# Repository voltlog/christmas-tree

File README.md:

# Voltlog Smart Christmas Tree

This was my attempt at creating a smart Christmass tree decoration. I wanted to have a bunch of RGB LEDs that I could control remotely from my smart home automation system so I created this board using 11 x SK6812-EC20 RGB LEDs connected with an ESP32. The board can be flashed with an arduino sketch and have it flash various patterns in a standalone operating mode or you can flash it with esphome (or other similar platforms) and have it controlled from your smart home system.

More info about this project in [Voltlog #344](https://youtu.be/laZLzfCeY8s).
This was available in a limitted edition in the [Voltlog Tindie Store](https://www.tindie.com/products/voltlog/voltlog-smart-christmas-tree/).

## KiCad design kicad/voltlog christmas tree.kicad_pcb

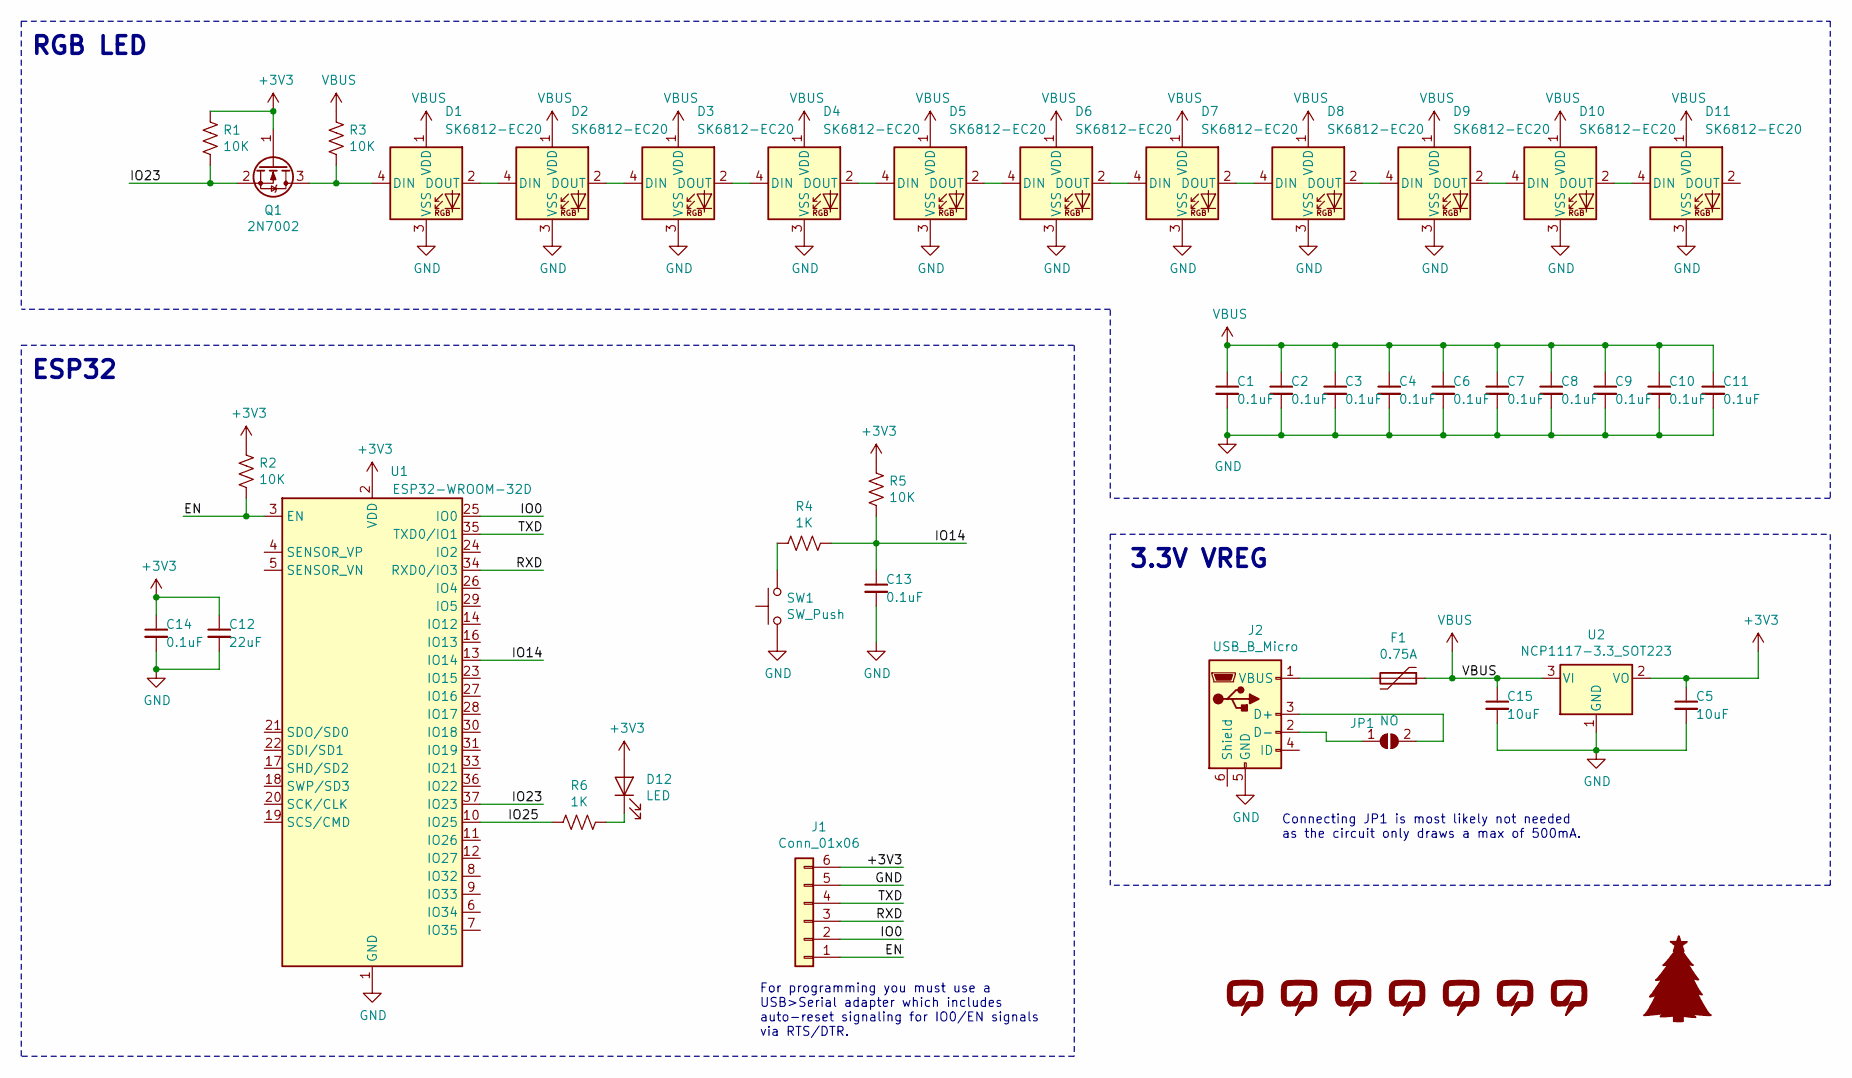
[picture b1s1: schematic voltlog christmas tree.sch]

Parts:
C1, C2, C3, C4, C6, C7, C8, C9, C10, C11, C13, C14: 0.1uF; C_0805_2012Metric
C5, C15: 10uF; C_0805_2012Metric
C12: 22uF; C_0805_2012Metric
D1, D2, D3, D4, D5, D6, D7, D8, D9, D10, D11: SK6812-EC20; sk6812-2020
D12: LED; LED_0805_2012Metric
F1: 0.75A; Fuse_0805_2012Metric
J1: Conn_01x06; JST_SH_BM06B-SRSS-TB_1x06-1MP_P1.00mm_Vertical
J2: USB_B_Micro; USB_Micro-B_Molex-105017-0001
JP1: NO; SolderJumper-2_P1.3mm_Open_RoundedPad1.0x1.5mm
Q1: 2N7002; SOT-23
R1, R2, R3, R5: 10K; R_0805_2012Metric
R4, R6: 1K; R_0805_2012Metric
SW1: SW_Push; SW_Push_1P1T_NO_6x6mm_H9.5mm
T1: ChristmasTree; test
U1: ESP32-WROOM-32D; ESP32-WROOM-32
U2: NCP1117-3.3_SOT223; SOT-223-3_TabPin2
V1, V2, V3, V4, V5, V6, V8: VOLTLOG_LOGO; voltlog_mask_5mm

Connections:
+3V3: C5.1, C12.1, C14.1, D12.2 (A), J1.6, Q1.1 (G), R1.1, R2.1, R5.1, U1.2 (VDD), U2.2 (VO)
/EN: J1.1, R2.2, U1.3 (EN)
/IO0: J1.2, U1.25 (IO0)
/IO14: C13.1, R4.1, R5.2, U1.13 (IO14)
/IO23: Q1.2 (S), R1.2, U1.37 (IO23)
/IO25: R6.2, U1.10 (IO25)
/RXD: J1.3, U1.34 (RXD0/IO3)
/TXD: J1.4, U1.35 (TXD0/IO1)
GND: C1.2, C2.2, C3.2, C4.2, C5.2, C6.2, C7.2, C8.2, C9.2, C10.2, C11.2, C12.2, C13.2, C14.2, C15.2, D1.3 (VSS), D2.3 (VSS), D3.3 (VSS), D4.3 (VSS), D5.3 (VSS), D6.3 (VSS), D7.3 (VSS), D8.3 (VSS), D9.3 (VSS), D10.3 (VSS), D11.3 (VSS), J1.5, J2.5 (GND), SW1.1, U1.1 (GND), U1.15 (GND), U1.38 (GND), U1.39 (GND), U2.1 (GND)
unnamed: D1.2 (DOUT), D2.4 (DIN)
unnamed: D1.4 (DIN), Q1.3 (D), R3.2
unnamed: D2.2 (DOUT), D3.4 (DIN)
unnamed: D3.2 (DOUT), D4.4 (DIN)
unnamed: D4.2 (DOUT), D5.4 (DIN)
unnamed: D5.2 (DOUT), D6.4 (DIN)
unnamed: D6.2 (DOUT), D7.4 (DIN)
unnamed: D7.2 (DOUT), D8.4 (DIN)
unnamed: D8.2 (DOUT), D9.4 (DIN)
unnamed: D10.2 (DOUT), D11.4 (DIN)
unnamed: D9.2 (DOUT), D10.4 (DIN)
unnamed: D12.1 (K), R6.1
unnamed: F1.2, J2.1 (VBUS)
unnamed: J2.2 (D-), JP1.1 (A)
unnamed: J2.3 (D+), JP1.2 (B)
unnamed: R4.2, SW1.2
VBUS: C1.1, C2.1, C3.1, C4.1, C6.1, C7.1, C8.1, C9.1, C10.1, C11.1, C15.1, D1.1 (VDD), D2.1 (VDD), D3.1 (VDD), D4.1 (VDD), D5.1 (VDD), D6.1 (VDD), D7.1 (VDD), D8.1 (VDD), D9.1 (VDD), D10.1 (VDD), D11.1 (VDD), F1.1, R3.1, U2.3 (VI)

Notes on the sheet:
ESP32
3.3V VREG
RGB LED
For programming you must use a USB>Serial adapter which includes auto-reset signaling for IO0/EN signals via RTS/DTR.
Connecting JP1 is most likely not needed as the circuit only draws a max of 500mA.

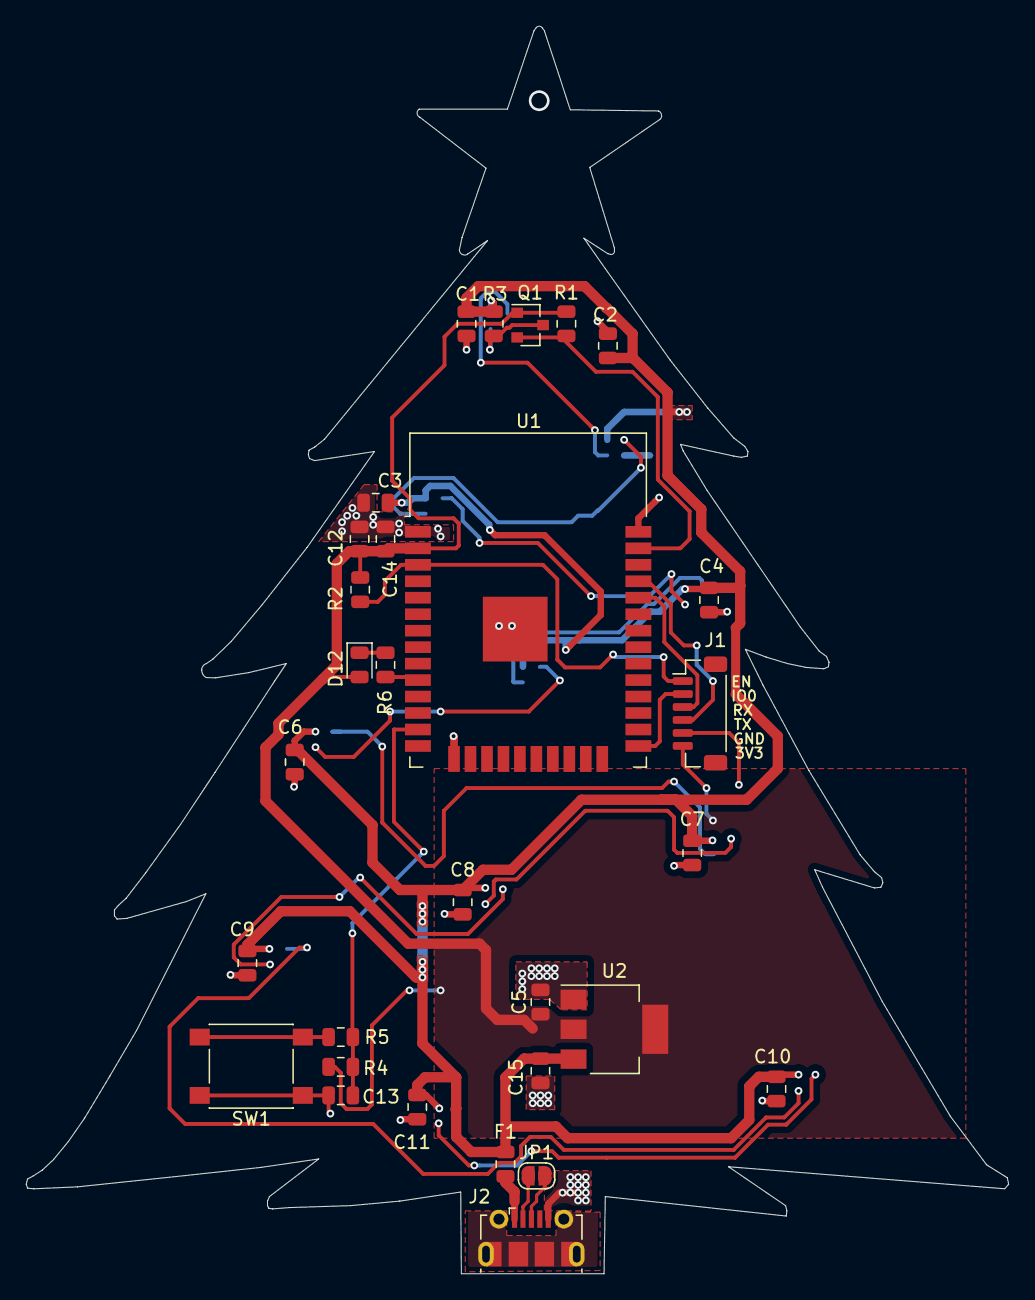
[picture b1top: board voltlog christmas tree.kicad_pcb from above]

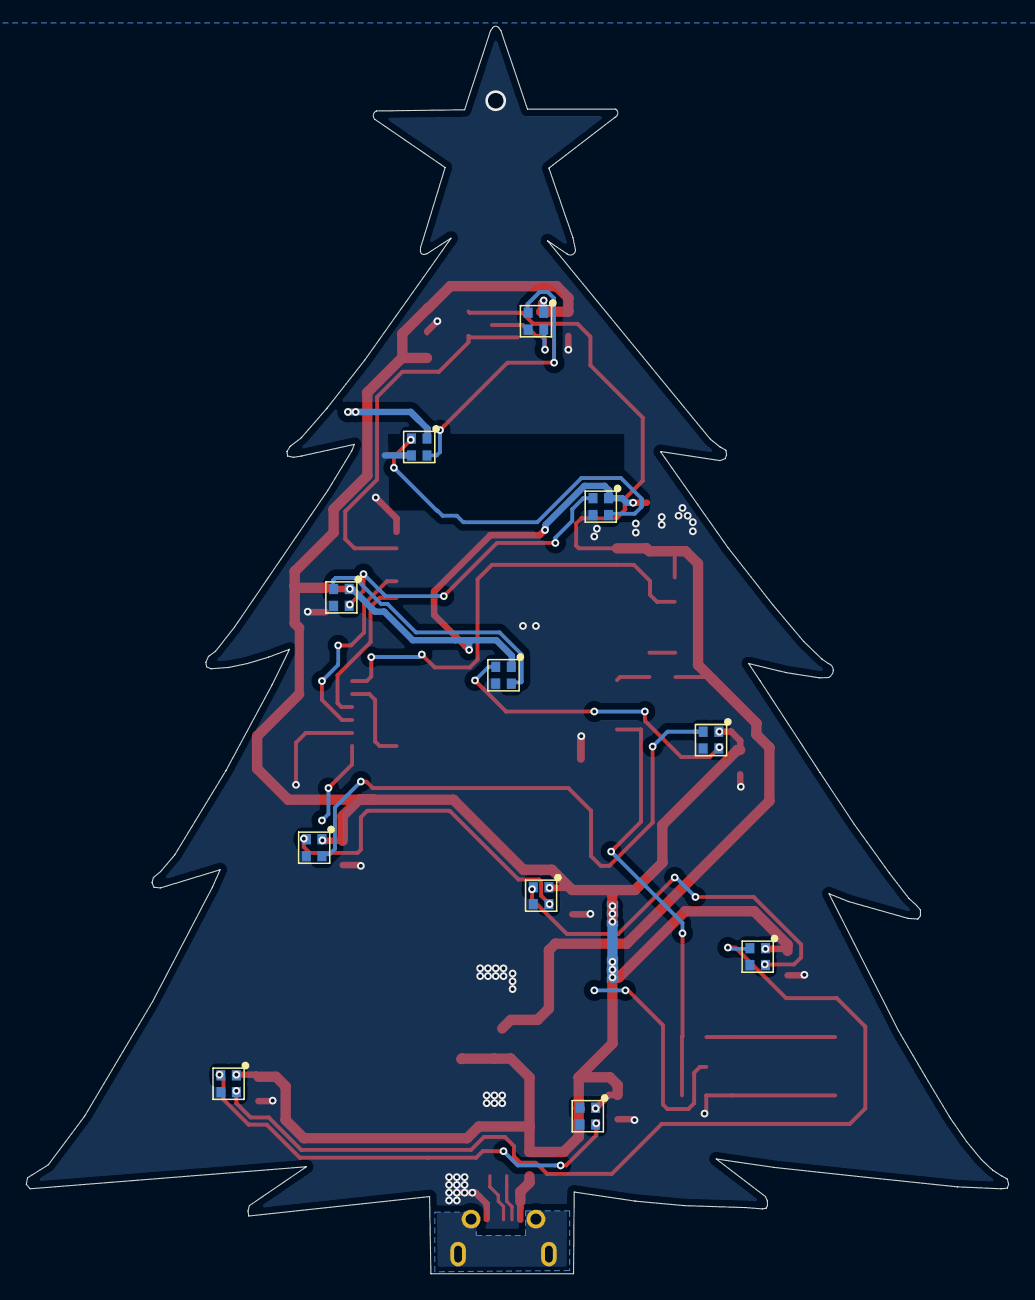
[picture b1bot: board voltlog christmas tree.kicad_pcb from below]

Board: 2 copper layers, 75.8 x 96.2 mm, 49 parts (17 on the bottom side), 26 nets.

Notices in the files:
kicad/voltlog christmas tree.sch:
License: CERN-OHL-P
